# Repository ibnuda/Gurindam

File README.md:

# Gurindam

it's an [arisu](https://github.com/FateNozomi/arisu-pcb)-style keyboard that uses
a promicro as the controller.

## About the name
[Gurindam](https://en.wikipedia.org/wiki/Gurindam) (Jawi: ڬوريندام) is a type of
irregular verse forms of traditional Indonesian and Malay poetry.
It is a combination of two clauses where the relative clause forms a line and is
thus linked to the second line, or the main clause.
Each pair of lines (stanza) provides complete ideas within the pair and has the
same rhyme in its end.
There is no limit on the number words per line and neither the rhythm per line is fixed.

## About the silks

The silk is Gurindam Dua Belas (Twelve Gurindam) of [Raja Ali Haji](https://en.wikipedia.org/wiki/Raja_Ali_Haji) written in 1847.

## My plea
If somehow you fabricate this design, I hope that you feed a filling meal to one
of your less-fortunate neighbours.

## License
CERN Open Hardware Licence Version 2 - Strongly Reciprocal

### Notes
If you have fabricated the pcb using these files prior 2022-01-25 and want to use
the plates in the `sandwich` directory, use plate v1 or v2.
But, if you fabricated the pcb using the files after 2022-01-25 and want to use
the plates in the `sandwich` directory, use v3.

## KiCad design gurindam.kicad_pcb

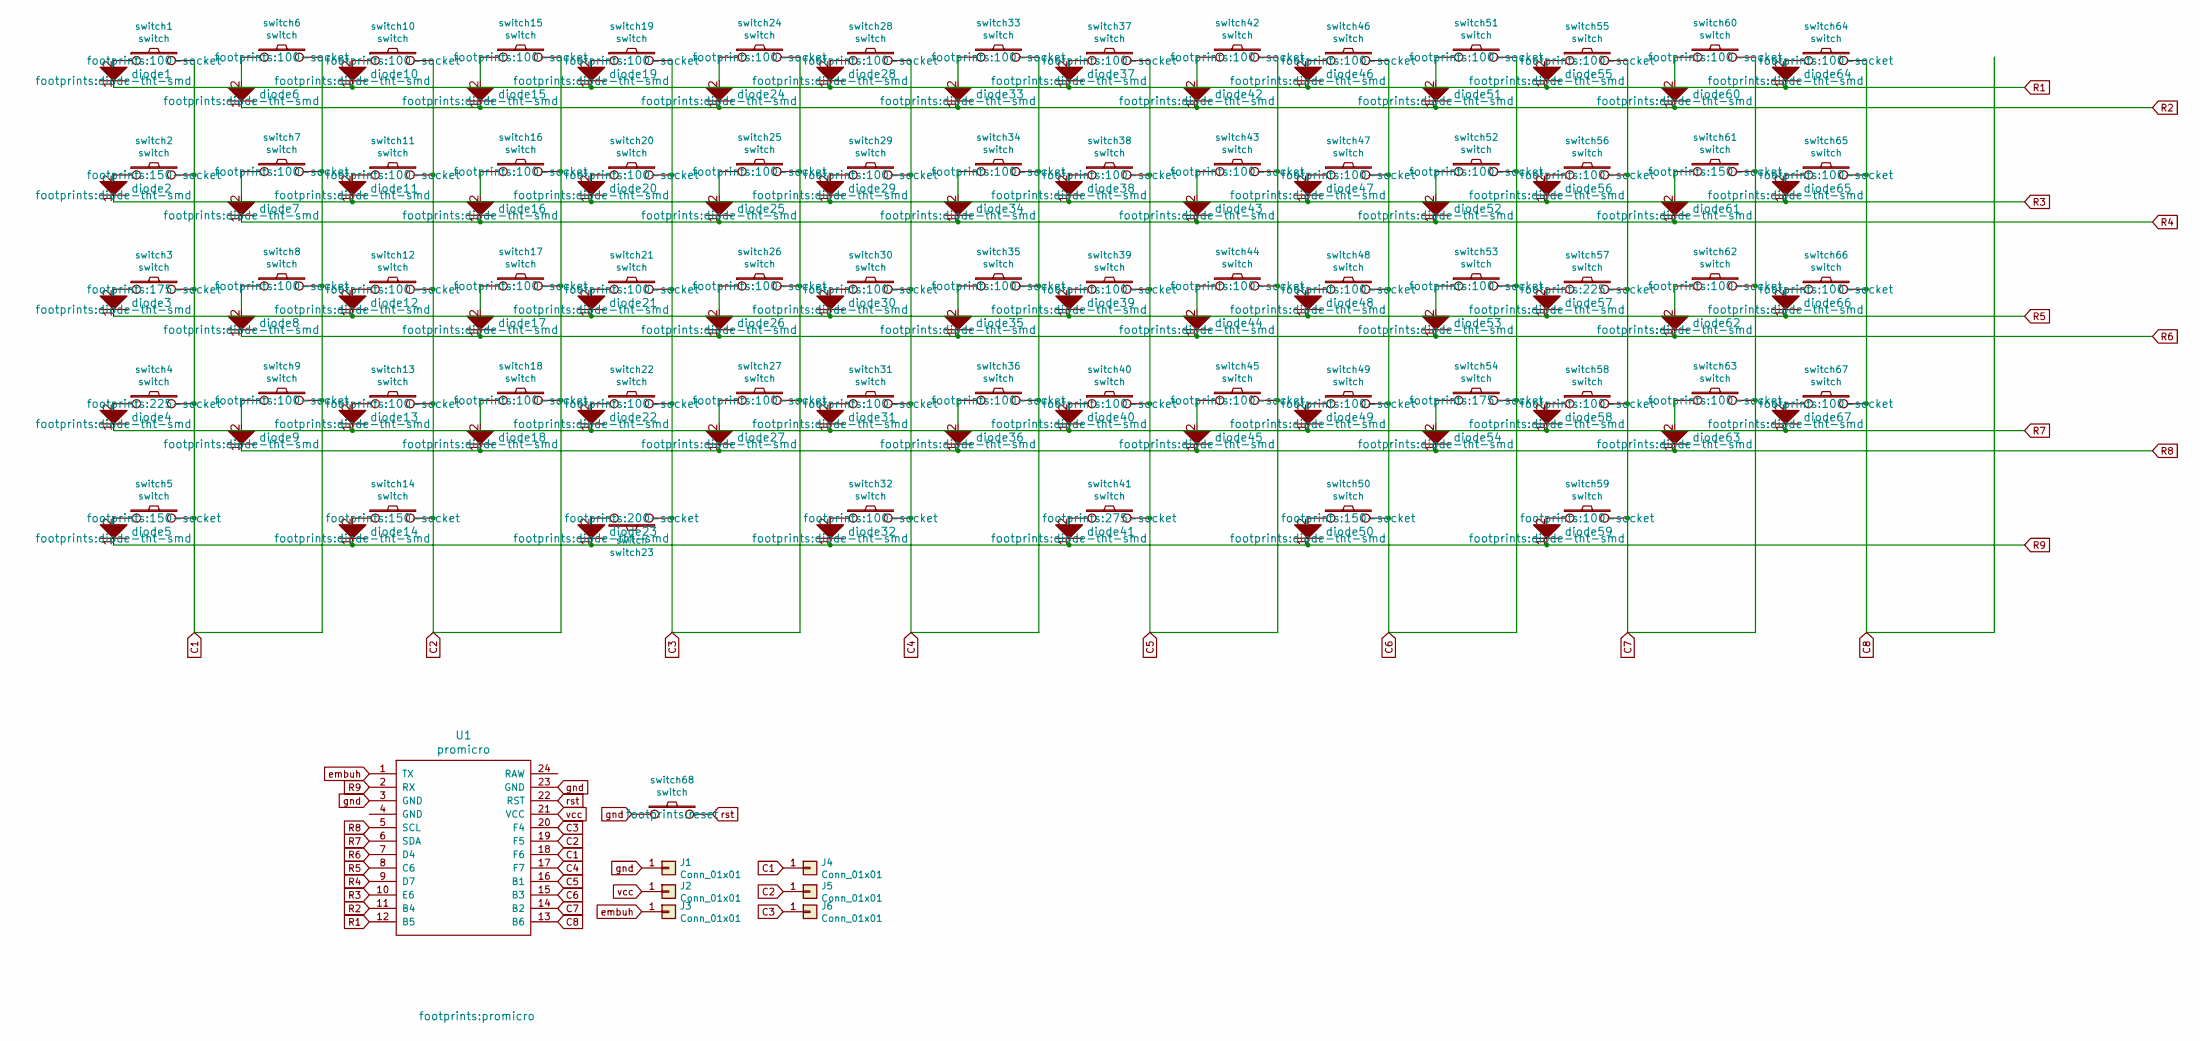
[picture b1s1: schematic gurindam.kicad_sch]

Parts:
J1, J2, J3, J4, J5, J6: Conn_01x01; wirepad
U1: promicro
diode1, diode2, diode3, diode4, diode5, diode6, diode7, diode8, diode9, diode10, diode11, diode12, diode13, diode14, diode15, diode16, diode17, diode18, diode19, diode20, diode21, diode22, diode23, diode24, diode25, diode26, diode27, diode28, diode29, diode30, diode31, diode32, diode33, diode34, diode35, diode36, diode37, diode38, diode39, diode40, diode41, diode42, diode43, diode44, diode45, diode46, diode47, diode48, diode49, diode50, diode51, diode52, diode53, diode54, diode55, diode56, diode57, diode58, diode59, diode60, diode61, diode62, diode63, diode64, diode65, diode66, diode67: diode; diode-tht-smd
switch1, switch6, switch7, switch8, switch9, switch10, switch11, switch12, switch13, switch15, switch16, switch17, switch18, switch19, switch20, switch21, switch22, switch24, switch25, switch26, switch27, switch28, switch29, switch30, switch31, switch32, switch33, switch34, switch35, switch36, switch37, switch38, switch39, switch40, switch42, switch43, switch44, switch45, switch46, switch47, switch48, switch49, switch51, switch52, switch53, switch55, switch56, switch58, switch59, switch60, switch62, switch63, switch64, switch65, switch66, switch67: switch; 100-socket
switch2, switch5, switch14, switch50, switch61: switch; 150-socket
switch3, switch54: switch; 175-socket
switch4, switch57: switch; 225-socket
switch23: switch; 200-socket
switch41: switch; 275-socket
switch68: switch; reset

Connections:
C1: J4.1, U1.18 (F6), switch1.2, switch2.2, switch3.2, switch4.2, switch5.2, switch6.2, switch7.2, switch8.2, switch9.2
C2: J5.1, U1.19 (F5), switch10.2, switch11.2, switch12.2, switch13.2, switch14.2, switch15.2, switch16.2, switch17.2, switch18.2
C3: J6.1, U1.20 (F4), switch19.2, switch20.2, switch21.2, switch22.2, switch23.1, switch24.2, switch25.2, switch26.2, switch27.2
C4: U1.17 (F7), switch28.2, switch29.2, switch30.2, switch31.2, switch32.2, switch33.2, switch34.2, switch35.2, switch36.2
C5: U1.16 (B1), switch37.2, switch38.2, switch39.2, switch40.2, switch41.2, switch42.2, switch43.2, switch44.2, switch45.2
C6: U1.15 (B3), switch46.2, switch47.2, switch48.2, switch49.2, switch50.2, switch51.2, switch52.2, switch53.2, switch54.2
C7: U1.14 (B2), switch55.2, switch56.2, switch57.2, switch58.2, switch59.2, switch60.2, switch61.2, switch62.2, switch63.2
C8: U1.13 (B6), switch64.2, switch65.2, switch66.2, switch67.2
unnamed: diode1.2, switch1.1
unnamed: diode2.2, switch2.1
unnamed: diode3.2, switch3.1
unnamed: diode4.2, switch4.1
unnamed: diode5.2, switch5.1
unnamed: diode6.2, switch6.1
unnamed: diode7.2, switch7.1
unnamed: diode8.2, switch8.1
unnamed: diode9.2, switch9.1
unnamed: diode10.2, switch10.1
unnamed: diode11.2, switch11.1
unnamed: diode12.2, switch12.1
unnamed: diode13.2, switch13.1
unnamed: diode14.2, switch14.1
unnamed: diode15.2, switch15.1
unnamed: diode16.2, switch16.1
unnamed: diode17.2, switch17.1
unnamed: diode18.2, switch18.1
unnamed: diode19.2, switch19.1
unnamed: diode20.2, switch20.1
unnamed: diode21.2, switch21.1
unnamed: diode22.2, switch22.1
unnamed: diode23.2, switch23.2
unnamed: diode24.2, switch24.1
unnamed: diode25.2, switch25.1
unnamed: diode26.2, switch26.1
unnamed: diode27.2, switch27.1
unnamed: diode28.2, switch28.1
unnamed: diode29.2, switch29.1
unnamed: diode30.2, switch30.1
unnamed: diode31.2, switch31.1
unnamed: diode32.2, switch32.1
unnamed: diode33.2, switch33.1
unnamed: diode34.2, switch34.1
unnamed: diode35.2, switch35.1
unnamed: diode36.2, switch36.1
unnamed: diode37.2, switch37.1
unnamed: diode38.2, switch38.1
unnamed: diode39.2, switch39.1
unnamed: diode40.2, switch40.1
unnamed: diode41.2, switch41.1
unnamed: diode42.2, switch42.1
unnamed: diode43.2, switch43.1
unnamed: diode44.2, switch44.1
unnamed: diode45.2, switch45.1
unnamed: diode46.2, switch46.1
unnamed: diode47.2, switch47.1
unnamed: diode48.2, switch48.1
unnamed: diode49.2, switch49.1
unnamed: diode50.2, switch50.1
unnamed: diode51.2, switch51.1
unnamed: diode52.2, switch52.1
unnamed: diode53.2, switch53.1
unnamed: diode54.2, switch54.1
unnamed: diode55.2, switch55.1
unnamed: diode56.2, switch56.1
unnamed: diode57.2, switch57.1
unnamed: diode58.2, switch58.1
unnamed: diode59.2, switch59.1
unnamed: diode60.2, switch60.1
unnamed: diode61.2, switch61.1
unnamed: diode62.2, switch62.1
unnamed: diode63.2, switch63.1
unnamed: diode64.2, switch64.1
unnamed: diode65.2, switch65.1
unnamed: diode66.2, switch66.1
unnamed: diode67.2, switch67.1
R1: U1.12 (B5), diode1.1, diode10.1, diode19.1, diode28.1, diode37.1, diode46.1, diode55.1, diode64.1
R2: U1.11 (B4), diode6.1, diode15.1, diode24.1, diode33.1, diode42.1, diode51.1, diode60.1
R3: U1.10 (E6), diode2.1, diode11.1, diode20.1, diode29.1, diode38.1, diode47.1, diode56.1, diode65.1
R4: U1.9 (D7), diode7.1, diode16.1, diode25.1, diode34.1, diode43.1, diode52.1, diode61.1
R5: U1.8 (C6), diode3.1, diode12.1, diode21.1, diode30.1, diode39.1, diode48.1, diode57.1, diode66.1
R6: U1.7 (D4), diode8.1, diode17.1, diode26.1, diode35.1, diode44.1, diode53.1, diode62.1
R7: U1.6 (SDA), diode4.1, diode13.1, diode22.1, diode31.1, diode40.1, diode49.1, diode58.1, diode67.1
R8: U1.5 (SCL), diode9.1, diode18.1, diode27.1, diode36.1, diode45.1, diode54.1, diode63.1
R9: U1.2 (RX), diode5.1, diode14.1, diode23.1, diode32.1, diode41.1, diode50.1, diode59.1
embuh: J3.1, U1.1 (TX)
gnd: J1.1, U1.3 (GND), U1.23 (GND), switch68.1
rst: U1.22 (RST), switch68.2
vcc: J2.1, U1.21 (VCC)

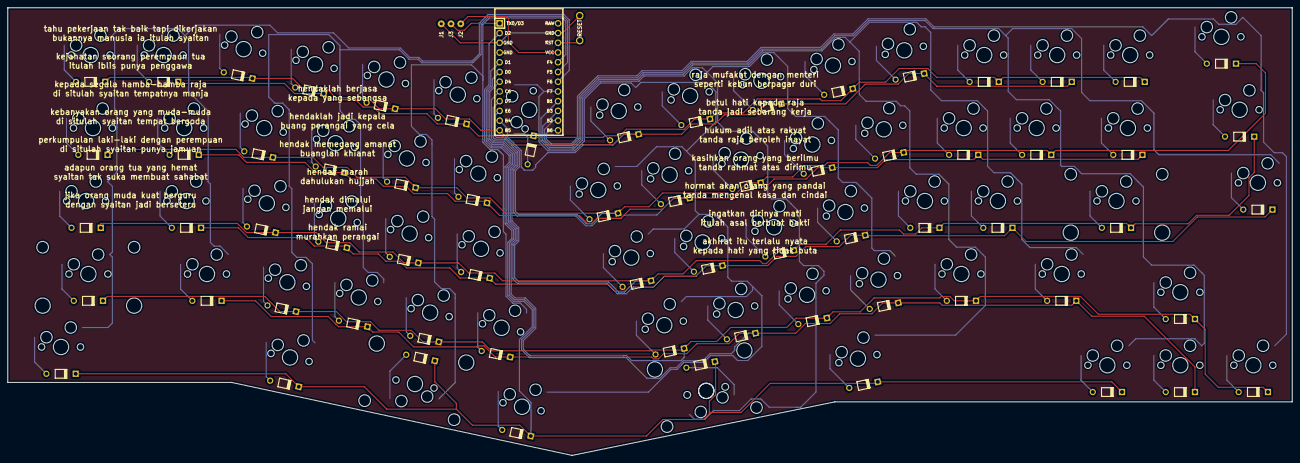
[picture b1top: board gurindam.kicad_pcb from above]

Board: 2 copper layers, 335.3 x 116.8 mm, 139 parts (0 on the bottom side), 88 nets.

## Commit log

2021-11-26 init commit.
2021-11-27 wired the columns.
2021-11-27 finished.
2021-11-27 license and readme.
2021-11-27 screenshot.
2021-11-30 hotswap socket.
2021-12-01 stacked acrylic case.
2021-12-10 fixed 275.
2021-12-23 stacked acry. v2.
2022-01-26 kicad 6 and moved the rightside 2mm.
2022-02-04 plates v3.
2022-02-04 just to cover my ass in case someone is butthurt.
